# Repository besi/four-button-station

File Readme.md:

# Four button station

Control four Relays.

**WARNING**: This project uses 230V. Please be careful and use these resources at your own risk.

## Flashing

The used ESP-07 chip uses 1MB of flash so make sure to flash it with the [1MB flash image](https://micropython.org/download/ESP8266_GENERIC/).

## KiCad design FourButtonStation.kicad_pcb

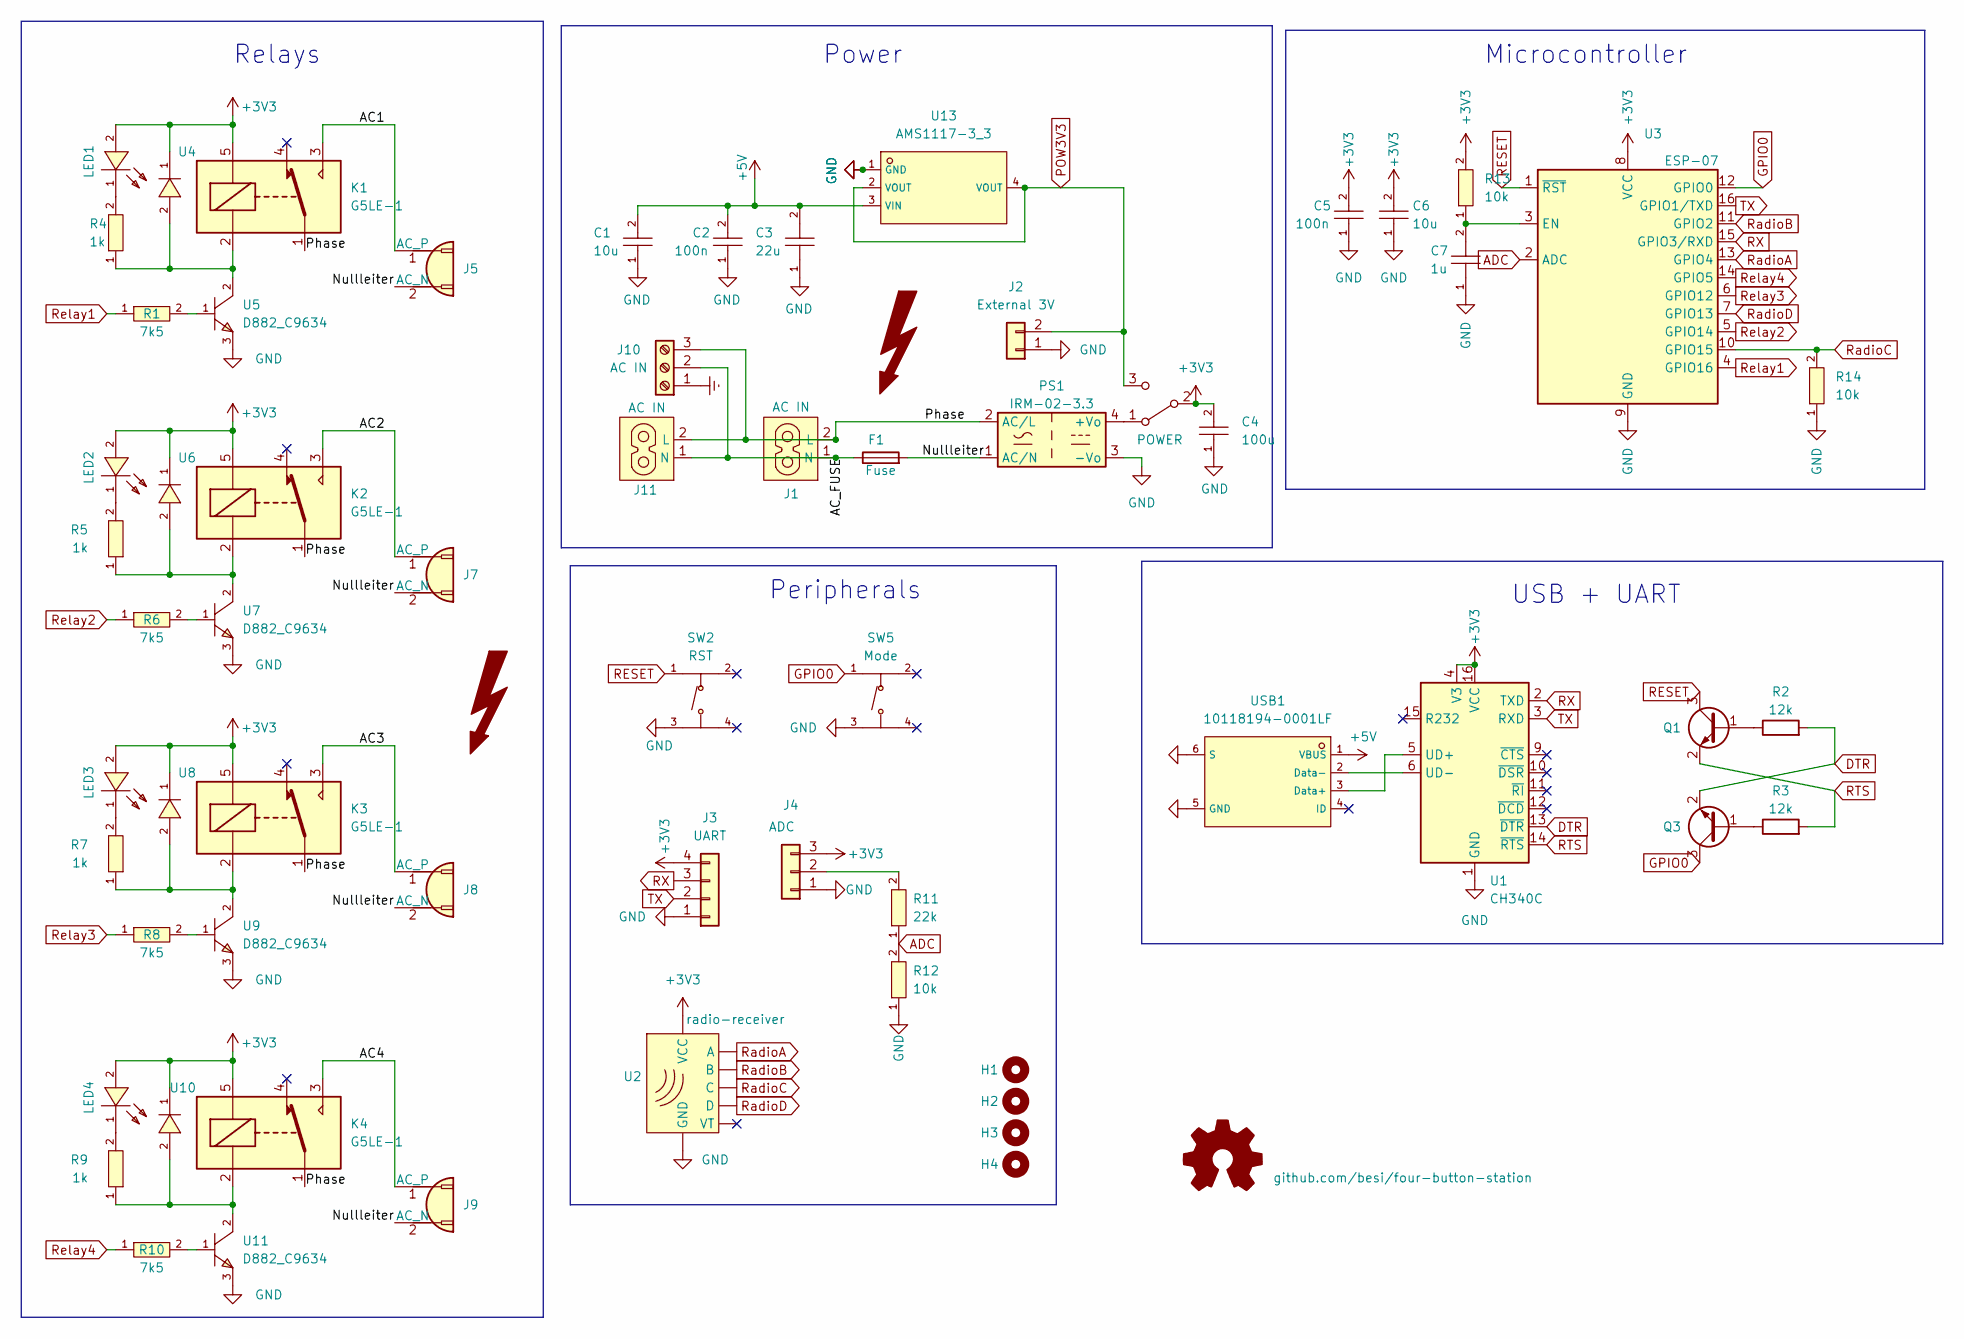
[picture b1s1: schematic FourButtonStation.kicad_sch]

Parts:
C1, C6: 10u; C0402; LCSC C15525
C2, C5: 100n; C0402; LCSC C1525
C3: 22u; C0603; LCSC C59461
C4: 100u; C1206; LCSC C15008
C7: 1u; C0603; LCSC C15849
F1: Fuse; Fuseholder_Cylinder-5x20mm_Schurter_0031_8201_Horizontal_Op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
H1, H2, H3, H4: MountingHole; MountingHole_3.2mm_M3
J1: AC IN; c8-inlet-old
J2: External 3V; PinHeader_1x02_P2.54mm_Vertical
J3: UART; PinHeader_1x04_P2.54mm_Vertical
J4: ADC; PinHeader_1x03_P2.54mm_Vertical
J5, J7, J8, J9: Conn_WallSocket; TerminalBlock_Phoenix_MKDS-1,5-2_1x02_P5.00mm_Horizontal
J10: AC IN; TerminalBlock_Phoenix_MKDS-1,5-3-5.08_1x03_P5.08mm_Horizont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
J11: AC IN; c8-inlet
K1, K2, K3, K4: G5LE-1; Relay_SPDT_Omron-G5LE-1
LED1, LED2, LED3, LED4: KT-0603R; LED0603-RD; LCSC C2286
Logo1: github.com/besi/four-button-station; OSHW-Symbol_6.7x6mm_SilkScreen
PS1: IRM-02-3.3; Converter_ACDC_MeanWell_IRM-05-xx_THT
Q1, Q3: MMBT3904; SOT-23-3_L2.9-W1.3-P1.90-LS2.4-BR; LCSC C20526
R1, R6, R8, R10: 7k5; R0603; LCSC C23234
R2, R3: 12k; R0402; LCSC C25752
R4, R5, R7, R9: 1k; R0402; LCSC C11702
R11: 22k; R0603; LCSC C31850
R12, R13, R14: 10k; R0603; LCSC C25804
SW1: POWER; as12ap
SW2: RST; SW-SMD_4P-L5.1-W5.1-P3.70-LS6.5-TL-2; LCSC C318884
SW5: Mode; SW-SMD_4P-L5.1-W5.1-P3.70-LS6.5-TL-2; LCSC C318884
SYM1: SYM_Flash_XLarge
Sym3: SYM_Flash_XLarge
U1: CH340C; SOP-16_L10.0-W3.9-P1.27-LS6.0-BL; LCSC C7464026
U2: radio-receiver
U3: ESP-07; WIFIM-SMD_ESP-07; LCSC C82894
U4, U6, U8, U10: SM4007PL; SOD-123F_L2.8-W1.8-LS3.7-RD; LCSC C64898
U5, U7, U9, U11: D882_C9634; SOT-89-3_L4.5-W2.5-P1.50-LS4.2-BR; LCSC C9634
U13: AMS1117-3_3; SOT-223-3_L6.5-W3.4-P2.30-LS7.0-BR; LCSC C6186
USB1: 10118194-0001LF; MICRO-USB-SMD_10118194-0001LF; LCSC C132563

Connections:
+3V3: C4.2, C5.2, C6.2, J3.4, J4.3, K1.5, K2.5, K3.5, K4.5, LED1.2 (A), LED2.2 (A), LED3.2 (A), LED4.2 (A), R13.2, SW1.2 (B), U1.4 (V3), U1.16 (VCC), U2.2 (VCC), U3.8 (VCC), U4.1 (C), U6.1 (C), U8.1 (C), U10.1 (C)
+5V: C1.2, C2.2, C3.2, U13.3 (VIN), USB1.1 (VBUS)
/AC1: J5.1 (AC_P), K1.3
/AC2: J7.1 (AC_P), K2.3
/AC3: J8.1 (AC_P), K3.3
/AC4: J9.1 (AC_P), K4.3
/AC_FUSE: F1.1, J1.1 (N), J10.2, J11.1 (N)
/Nullleiter: F1.2, J5.2 (AC_N), J7.2 (AC_N), J8.2 (AC_N), J9.2 (AC_N), PS1.1 (AC/N)
/Phase: J1.2 (L), J10.3, J11.2 (L), K1.1, K2.1, K3.1, K4.1, PS1.2 (AC/L)
ADC: R11.1, R12.2, U3.2 (ADC)
DTR: Q3.2 (E), R2.2, U1.13 (~DTR)
Earth: J10.1
GND: C1.1, C2.1, C3.1, C4.1, C5.1, C6.1, C7.1, J2.1, J3.1, J4.1, PS1.3 (-Vo), R12.1, R14.1, SW2.3 (C), SW5.3 (C), U1.1 (GND), U2.1 (GND), U3.9 (GND), U5.3 (E), U7.3 (E), U9.3 (E), U11.3 (E), U13.1 (GND), USB1.5 (GND), USB1.6 (S)
GPIO0: Q3.3 (C), SW5.1 (A), U3.12 (GPIO0)
unnamed: J4.2, R11.2
unnamed: LED1.1 (K), R4.2
unnamed: LED2.1 (K), R5.2
unnamed: LED3.1 (K), R7.2
unnamed: LED4.1 (K), R9.2
unnamed: PS1.4 (+Vo), SW1.1 (A)
unnamed: Q1.1 (B), R2.1
unnamed: Q3.1 (B), R3.1
unnamed: U1.5 (UD+), USB1.3 (Data+)
unnamed: U1.6 (UD-), USB1.2 (Data-)
unnamed: C7.2, R13.1, U3.3 (EN)
unnamed: K1.2, R4.1, U4.2 (A), U5.2 (C)
unnamed: R1.2, U5.1 (B)
unnamed: K2.2, R5.1, U6.2 (A), U7.2 (C)
unnamed: R6.2, U7.1 (B)
unnamed: K3.2, R7.1, U8.2 (A), U9.2 (C)
unnamed: R8.2, U9.1 (B)
unnamed: K4.2, R9.1, U10.2 (A), U11.2 (C)
unnamed: R10.2, U11.1 (B)
POW3V3: J2.2, SW1.3 (C), U13.2 (VOUT), U13.4 (VOUT)
RESET: Q1.3 (C), SW2.1 (A), U3.1 (~RST)
RTS: Q1.2 (E), R3.2, U1.14 (~RTS)
RX: J3.3, U1.2 (TXD), U3.15 (GPIO3/RXD)
RadioA: U2.6 (A), U3.13 (GPIO4)
RadioB: U2.5 (B), U3.11 (GPIO2)
RadioC: R14.2, U2.4 (C), U3.10 (GPIO15)
RadioD: U2.3 (D), U3.7 (GPIO13)
Relay1: R1.1, U3.4 (GPIO16)
Relay2: R6.1, U3.5 (GPIO14)
Relay3: R8.1, U3.6 (GPIO12)
Relay4: R10.1, U3.14 (GPIO5)
TX: J3.2, U1.3 (RXD), U3.16 (GPIO1/TXD)

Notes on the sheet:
Relays
Microcontroller
Power
USB + UART
Peripherals

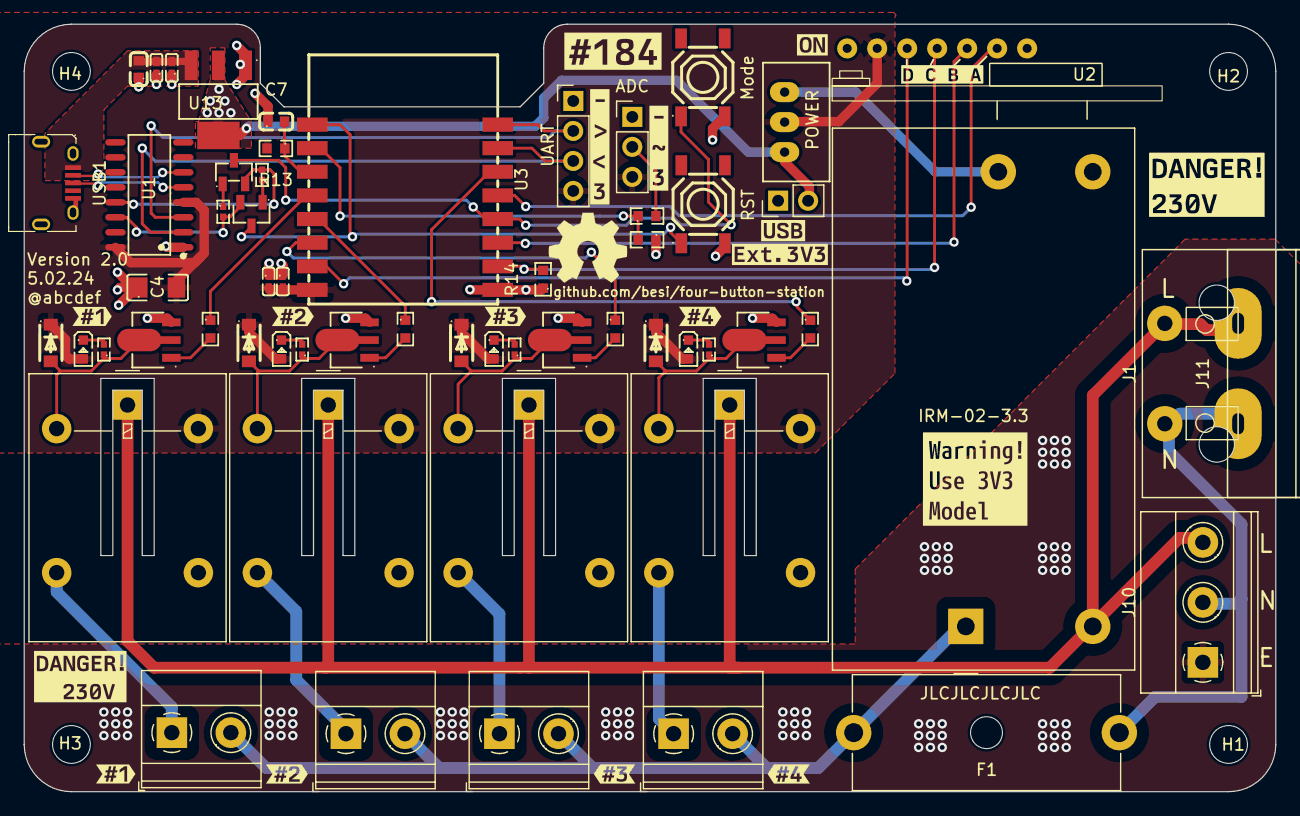
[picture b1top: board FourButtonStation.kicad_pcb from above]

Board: 2 copper layers, 106.0 x 65.0 mm, 82 parts (0 on the bottom side), 45 nets.

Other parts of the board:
kibuzzard-65EDF7BF: G***; kibuzzard-65EDF7BF
kibuzzard-65EDF79E: G***; kibuzzard-65EDF79E
kibuzzard-65EE27C8: G***; kibuzzard-65EE27C8
kibuzzard-65EE27E0: G***; kibuzzard-65EE27E0
kibuzzard-65EE35B8: G***; kibuzzard-65EE35B8
kibuzzard-65EE261E: G***; kibuzzard-65EE261E
kibuzzard-65EE278E: G***; kibuzzard-65EE278E
kibuzzard-65EE298C: G***; kibuzzard-65EE298C
kibuzzard-65EE2541: G***; kibuzzard-65EE2541
kibuzzard-65EE2549, kibuzzard-65EE2549#2: G***; kibuzzard-65EE2549
kibuzzard-65EE2550, kibuzzard-65EE2550#2: G***; kibuzzard-65EE2550
kibuzzard-65EE2558: G***; kibuzzard-65EE2558
kibuzzard-65EE2681: G***; kibuzzard-65EE2681
kibuzzard-65EE2746: G***; kibuzzard-65EE2746
kibuzzard-65F05324: G***; kibuzzard-65F05324
kibuzzard-67A2052C: G***; kibuzzard-67A2052C

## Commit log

2022-12-23 Update gitignore
2022-12-23 Update esp library
2022-12-25 Finalise the routing
2023-01-04 Add c8-inlet lib
    Status quo at fablab 1900
2023-01-04 Update c8 inlet and add GND connections on Front copper layer
2024-03-08 Schematic and routing
2024-03-10 Prepare for production
2024-03-11 Final tweaks
2024-03-11 Production files for 2.0
2024-03-11 Thermal conductivity for the AMS117
2024-03-11 Prepare release 2.0
2024-03-11 Initial software commit
2024-03-12 Update documentation and silkscreen
2024-03-12 Update version
2024-03-12 Add readme
2024-03-12 Add 10k pull up for enabling the esp
2024-12-28 Update schematic
2025-01-08 Re-arrange elements in Schematic to match the grid
2025-02-03 Cleanup Silkscreen and barcode
2025-02-04 Add another C8 Power entry AC plug as an option
2025-02-04 Fix erroneously matched 1k resistors
2025-02-04 Rule checks and Silkscreen
2025-02-04 Replace USB connector due to short fall
2025-02-04 Add drill origin
2025-02-05 Silk screen and add Earth Vias
2025-02-05 Prepare for deployment
2025-02-05 Prepare for upcoming version 2.1-beta
2025-02-05 Small silkscreen fixes
2025-02-05 Ignore fabrication plugin settings
2025-03-01 Add test code
2025-03-01 Switch to Kicad 8
2025-03-15 Add note about flash size
2025-03-15 Add boot code for connecting to the WIFI
2025-03-15 Allow switching on and off the relays by pressing the buttons
2025-03-15 Replace the 33k base resistors with 7k5 ones that are proven to work with the 3V3 Relays
    fixes #3
2025-03-15 Increase the diameter of the fuse holder holes to 1.6
    See #4
2025-03-15 Add note
    See #2
2025-03-15 Use the ADC(0) instead of Pin(2)
    See #2
2025-03-15 Send button presses to MQTT
2025-03-17 Publish button presses on MQTT
